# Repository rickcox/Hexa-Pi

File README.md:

# Hexa-Pi
A Compact 6 Compute Module Cluster

This is a PCB based project to create a very compact cluster of
Raspberry Pi CM4 compatible compute module boards.  It is quite bare-bones
in terms of peripheral support.  One of the modules - Module 5 - has a basic set of peripherals.
The other Modules - 0-4 - have only a small external connector for all I/O.
All 6 modules attach to a 1Gbit ethernet switch IC, which also has 2 off-board connectors.

It should be emphasized that **Compact Compute Cluster** is the focus of this design, not connectivity.
Connectivity, and peripheral support, has been reduced to meet the compact compute cluster goal.
Since all low voltage power, and the ethernet switch are on-board, a cluster of 6 Compute modules
can be supported with 1 12V DC power jack and 1 ethernet cable.
A 6 amp or larger 12V supply is recommended to support 6 running modules.

In addition, there are 2 external ethernet switch connectors, allowing boards to be "daisy chained".

The PCB is 150mm X 150mm X 1.6mm.  

A goal of this design is to be as Compute Module independent as possible, to allow
for a variety of compatible modules to be used.  Several of the Compute Module compatible
boards have been tested:

- 
  This board basically defigned the standard, so everything possible works on a Pi CM4.
  CM4 boards in the Module5 location may be either "Lite" or with EMMC.
  CM4 boards in the Module0-4 locations must have EMMC.
  
- 
  This RK3566 base board works well. 
  Rockchip processors for some odd reason must use 1.5Mbps on the serial console.  
  The pluggable EMMC modules makes setup of these boards very easy if you buy a cheap EMMC-microSD converter.

- 
  This Amlogic A311D based board is a bit faster than the Raspberry Pi CM4.
  These are a bit fussy to get setup, and OS selection is quite limited.

- 
  This RK3588 based board is **very** fast, if that is what you are looking for.
  There are "Lite" and "Full" versions of this board. Only he Full has been tested, but both should work.
  Use caution that the extra 3rd connector does not make contact with the Hexa-Pi PCB components.
  Again, Rockchip processors use 1.5Mbps on the serial console.
  OS selection is also limited here.
  Due to higher power consumption, a larger heatsink is recommended for the Radxa CM5.

- 
  **Testing TBD.**
  Not sure if serial port will work.
  The CM5 fan support is not compatible with CM4 or Hexa-Pi. The I2C fan controller can be used,
  as with a CM4

- Due to higher power consumption, a larger heatsink and possibly a heatspreader is recommended for the Raspberry Pi CM5.

Not all "compatible" boards have been tested.  
It is expected, unless the manufacturer has done something specific to make it incompatible, most "compatible" boards should work. 
Reviewing the datasheet and pinout on the 100 pin mezzanine connectors can be useful in spotting incompatibilities.

The Raspberry Pi CM4 boards have been most throughly tested.  
The other boards all have been verified to operate and connect via etherent, but all of the ports have not been tested.
Where known, incompatibilities have been noted.
It is recommended to initially configure an unfamiliar Compute Module in a Raspberry Pi CM4 IO board,
or board vendor specific baseboard, where all of the IO ports are available.
The Module5 location on the Hexa-Pi board may work for this, since it has USB, HDMI, and microSD
card support - but does not have the 40pin IO connector. 
Having a GUI is often helpful for the initial OS setup on a new board - even if your eventual use is headless.

Also, there is a small "Pi-Panel" support board that attaches to the external connectors 
at the top to provide a few simple peripherals for **all** of the Modules individually. 
A Green activity LED for each module is visible at the top, next to that module's connector.

There are also a Red power LED, a Yellow USB Overload LED, a White rpibboot mode LED, and a Blue NVME activity LED,
all on the main PCB, bottom edge.

Also included is stl files for a case for the Hexa-Pi board.
The PCB's were built, and mostly assembled, by JLCPCB.
The Case was 3D Printed. 

There is more information in the sub-directories:

- 
- 
- 

This work is licensed under the Creative Commons Attribution 4.0 International License. To view a copy of the license, visit https://creativecommons.org/licenses/by/4.0/

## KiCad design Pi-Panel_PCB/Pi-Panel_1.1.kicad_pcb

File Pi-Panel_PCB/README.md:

# Pi-Panel
A small "Front Panel" for the compute modules in the Hexa-Pi PCB.
5 of the modules have no other peripherals other than ethernet.

This is a small 36mm X 50mm PCB based that connects to the main Hexa-Pi board
using a 10 wire interface with JST connectors.

Since the individual Compute Modules on the main PCB are all powered together,
the goal with this board is to allow some basic repair and diagnosis if here are errors 
or failures on specific modules - without powering the main board down and disassembling the case!

The Activity LED for each module is adjacent and to the left of that board's conncetor.
The panel provides for each module individually:
- 5V and Gnd. Realistically about 500ma MAX can be pulled from 5V.
  **Warning** this is NOT current limited. 
  If you overload it, you will undervolt that Compute Module
- A Reset Push-Button for that specific CM.
- A serial console and CH340C USB to serial converter.
  You can directly plug into the USB-C connector and see a serial port.
  This connection uses the Raspberry 4 Compute Module serial interface pins -
  GPIO 14 (RxD) and GPIO 15(RxD). NOTE - some of the non-Raspberry Pi
  Compute modules default to different Serial console ports&pins
- A USB 2.0 port. This may be used to add any normal usb peripheral to the Pi.
  A USB Flash drive is the obvious usage, but anything USB2 compatible should work.
- An I2C port. This can be used for whatever desired.  
  This was initially envisioned as some sort of external display and maybe a couple
  buttons to control it.  Nothing has been developed here though, but
  there may be some interesting off-the-shelf options out there.
  The I2C is available on 3 Pi-Panel connectors:
  - A QWIIC Connector.
  - A Stemma-QT Style connector.
  - 0.1 inch headers.  Included is a 3.3V supply, which may be useful in some situations.
    This is a 250ma LDO off of the 5V supply, so remember the current **warning** above.

The connection to the main Hexa-Pi board uses a 10 pin JST GH 1.25mm connector.
Manufacturer partnumber SM10B-GHS-TB.  It is possible to buy pre-assembeled cables
with this mating connector. They can be purchased with connectors on both ends, or
having 1 end free.  Look for something like "GH 1.25MM 10P Single Ended" or "Double Ended".  
There are solderable holes on the Pi-Panel so the "Single Ended" type cable assemblies can be used,
and hand soldered on the Pi-Panel end.

Oh, and **one ugly secret!** The 10 pin JST connectors used between the Panel and main Hexa-Pi
board do not support any type of sequencing (Connect ground before anything else).
As a result, plugging the Pi-Panel into a running Hexa-Pi **MAY** result in the
connected Compute Module spontaneously resetting.  Being careful to have the Panel
grounded before plugging it in seems to minimize this anomaly!  
If another version of this board is done, this is on the list of things to try and fix, 
but you need to live with it for now.

This was developed in KiCad, and the design files are here.
The initial PCB's were built by JLCPCB, and partially assembled by them.
The through-hole parts and I2C connectors were hand assembled.

This PCB was small enough, that a panel of 2 was actually build.
Directory **production** has the 1 instance manufacturing data, and
directory **production-pnl** has the 2 instance manufacturing data.
At JLCPCB, both PCB's cost the same, since they are under 50mmX50mm.
The assembled 2 instance panel costs slightly more due
to the incremental cost of the parts - but you get 2 boards for the price of 1!

This work is licensed under the Creative Commons Attribution 4.0 International License. To view a copy of the license, visit https://creativecommons.org/licenses/by/4.0/

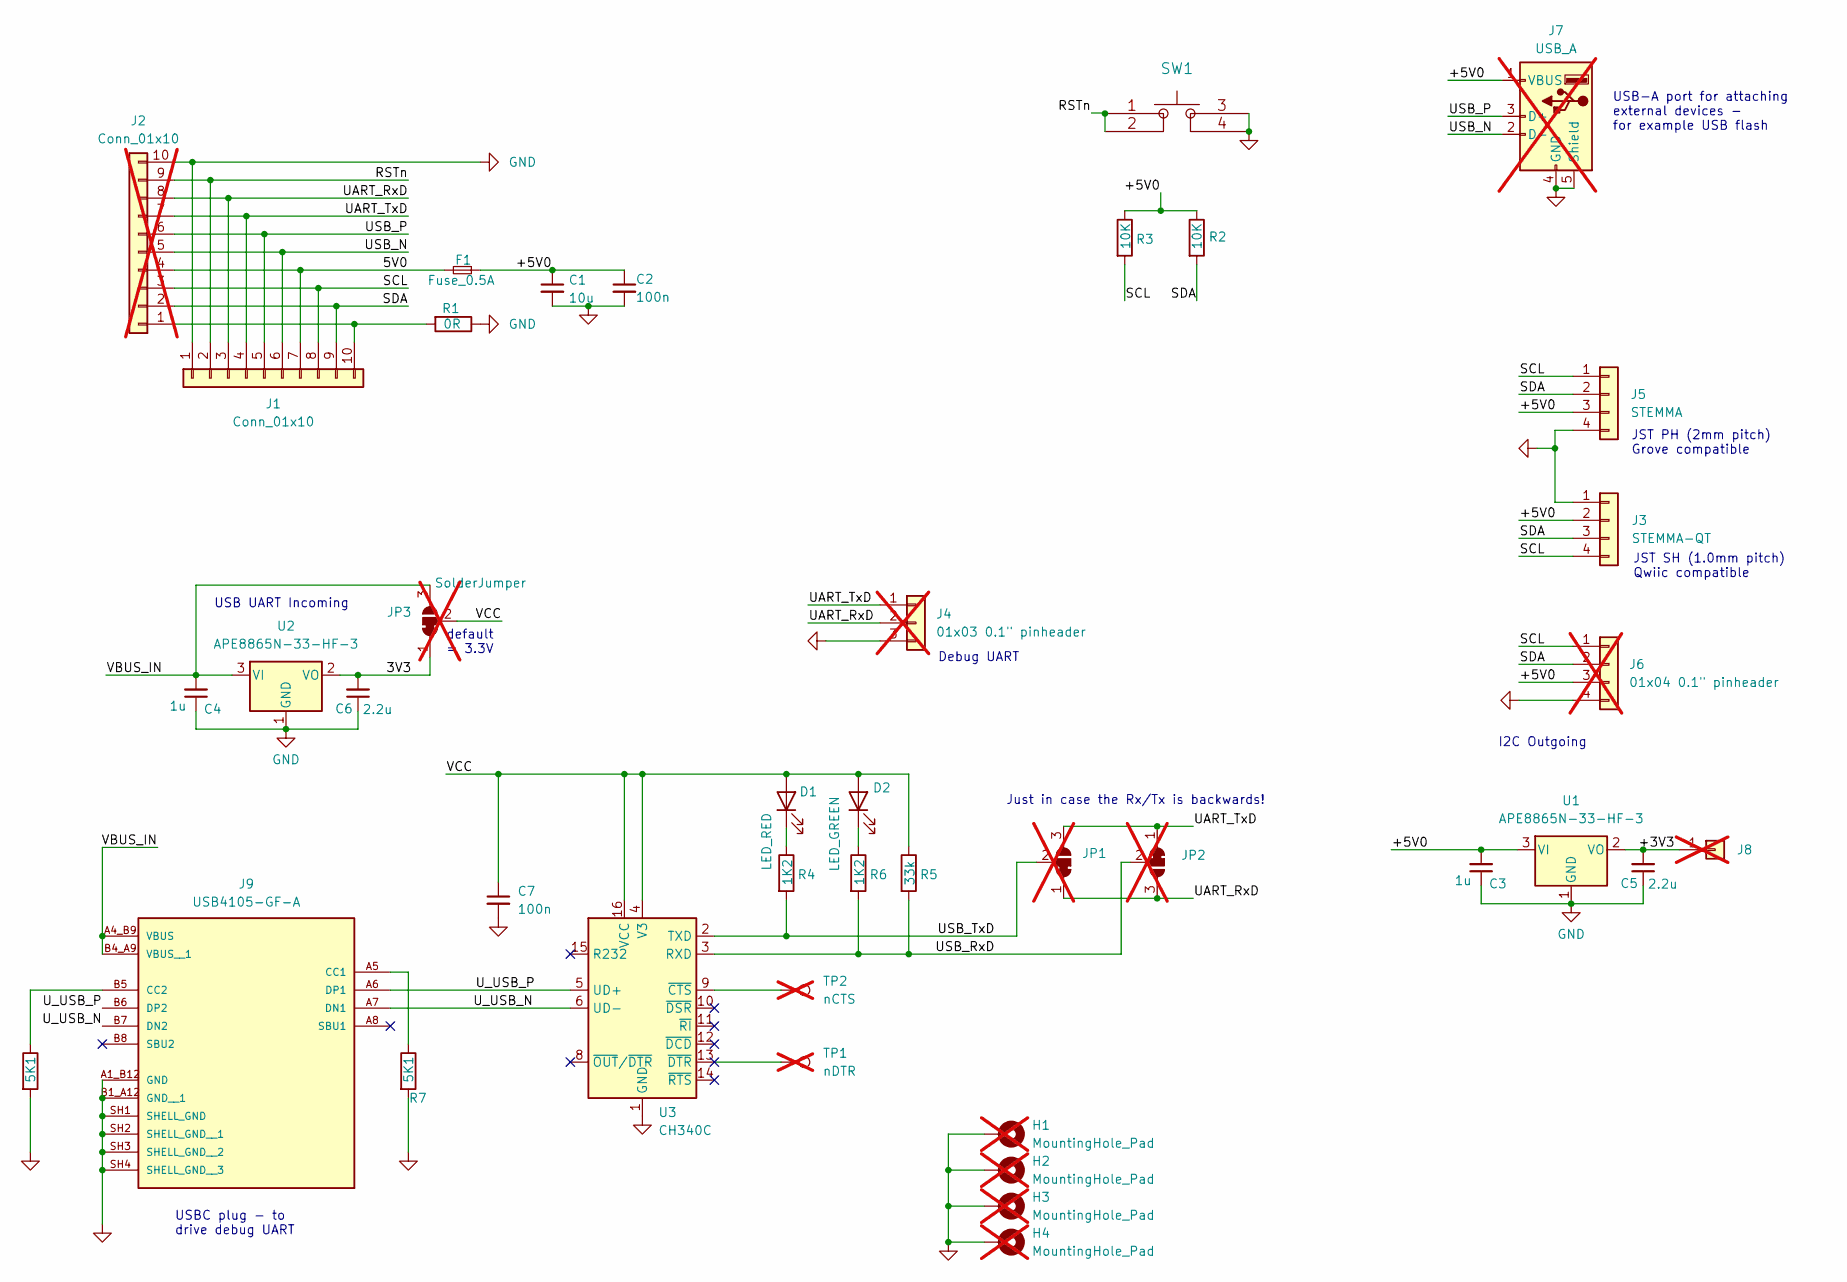
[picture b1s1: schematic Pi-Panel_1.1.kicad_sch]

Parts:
C1: 10u; C_0603_1608Metric; LCSC Part # C19702
C2, C7: 100n; C_0603_1608Metric; LCSC Part # C14663
C3, C4: 1u; C_0603_1608Metric; LCSC Part # C15849
C5, C6: 2.2u; C_0603_1608Metric; LCSC Part # C23630
D1: LED_RED; LED_0603_1608Metric; LCSC Part # C2286
D2: LED_GREEN; LED_0603_1608Metric; LCSC Part # C72038
F1: Fuse_0.5A; R_0603_1608Metric_Pad0.98x0.95mm_HandSolder; LCSC Part # C2960491
H1, H2, H3, H4: MountingHole_Pad; MountingHole_2.5mm_Pad_TopBottom; not fitted
J1: Conn_01x10; JST_GH_SM10B-GHS-TB_1x10-1MP_P1.25mm_Horizontal; Manuf Partno SM10B-GHS-TB; LCSC Part # C2683602
J2: Conn_01x10; PinHeader_1x10_P2.00mm_Vertical; not fitted
J3: STEMMA-QT; JST_SH_SM04B-SRSS-TB_1x04-1MP_P1.00mm_Horizontal; LCSC Part # C160404
J4: 01x03 0.1" pinheader; PinHeader_1x03_P2.54mm_Vertical; LCSC Part # TH; not fitted
J5: STEMMA; JST_PH_S4B-PH-SM4-TB_1x04-1MP_P2.00mm_Horizontal; LCSC Part # C265102
J6: 01x04 0.1" pinheader; PinHeader_1x04_P2.54mm_Vertical; LCSC Part # TH; not fitted
J7: USB_A; USB_A_Wuerth_614004134726_Horizontal; LCSC Part # TH; not fitted
J8: Conn_01x01; PinHeader_1x01_P2.54mm_Vertical; LCSC Part # TH; not fitted
J9: USB4105-GF-A; GCT_USB4105-GF-A; PARTREV B3; LCSC Part # C5184243
JP1, JP2, JP3: SolderJumper; SolderJumper-3_P1.3mm_Bridged12_RoundedPad1.0x1.5mm_NumberL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; not fitted
R1: 0R; R_0603_1608Metric_Pad0.98x0.95mm_HandSolder; LCSC Part # C21189
R2, R3: 10K; R_0603_1608Metric; LCSC Part # C25804
R4, R6: 1K2; R_0603_1608Metric; LCSC Part # C22765
R5: 33k; R_0603_1608Metric; LCSC Part # C4216
R7, R8: 5K1; R_0603_1608Metric; LCSC Part # C23186
SW1: pushButton-PTS647SM38SMTR2LFS; Part Description Tact Sw SPST-NO Top Actuated SMT 4.5mmX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; LCSC Part # C2689502
TP1: nDTR; TestPoint_Pad_1.0x1.0mm; not fitted
TP2: nCTS; TestPoint_Pad_1.0x1.0mm; not fitted
U1, U2: APE8865N-33-HF-3; SOT-23; LCSC Part # C296288
U3: CH340C; SOIC-16_3.9x9.9mm_P1.27mm; LCSC Part # C7464026

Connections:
/3V3: C6.2, JP3.1 (A), U2.2 (VO)
/5V0: F1.2, J1.7, J2.4
/+3V3: C5.2, J8.1, U1.2 (VO)
/+5V0: C1.1, C2.1, C3.2, F1.1, J3.2, J5.3, J6.3, J7.1 (VBUS), R2.1, R3.1, U1.3 (VI)
/RSTn: J1.2, J2.9, SW1.1, SW1.2
/SCL: J1.8, J2.3, J3.4, J5.1, J6.1, R3.2
/SDA: J1.9, J2.2, J3.3, J5.2, J6.2, R2.2
/UART_RxD: J1.3, J2.8, J4.2, JP1.1 (A), JP2.3 (B)
/UART_TxD: J1.4, J2.7, J4.1, JP1.3 (B), JP2.1 (A)
/USB_N: J1.6, J2.5, J7.2 (D-)
/USB_P: J1.5, J2.6, J7.3 (D+)
/USB_RxD: JP2.2 (C), R5.2, R6.2, U3.3 (RXD)
/USB_TxD: JP1.2 (C), R4.2, U3.2 (TXD)
/U_USB_N: J9.A7 (DN1), J9.B7 (DN2), U3.6 (UD-)
/U_USB_P: J9.A6 (DP1), J9.B6 (DP2), U3.5 (UD+)
/VBUS_IN: C4.2, J9.A4_B9 (VBUS), J9.B4_A9 (VBUS__1), JP3.3 (B), U2.3 (VI)
/VCC: C7.1, D1.2 (A), D2.2 (A), JP3.2 (C), R5.1, U3.4 (V3), U3.16 (VCC)
GND: C1.2, C2.2, C3.1, C4.1, C5.1, C6.1, C7.2, H1.1, H2.1, H3.1, H4.1, J1.1, J2.10, J3.1, J4.3, J5.4, J6.4, J7.4 (GND), J7.5 (Shield), J9.A1_B12 (GND), J9.B1_A12 (GND__1), J9.SH1 (SHELL_GND), J9.SH2 (SHELL_GND__1), J9.SH3 (SHELL_GND__2), J9.SH4 (SHELL_GND__3), R1.1, R7.2, R8.2, SW1.3, SW1.4, U1.1 (GND), U2.1 (GND), U3.1 (GND)
unnamed: D1.1 (K), R4.1
unnamed: D2.1 (K), R6.1
unnamed: J1.10, J2.1, R1.2
unnamed: J9.A5 (CC1), R7.1
unnamed: J9.B5 (CC2), R8.1
unnamed: TP2.1, U3.9 (~CTS)

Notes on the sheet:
I2C Outgoing
JST PH (2mm pitch) Grove compatible
USB-A port for attaching external devices - for example USB flash
Debug UART
USB UART Incoming
JST SH (1.0mm pitch) Qwiic compatible
default = 3.3V
USBC plug - to drive debug UART
Just in case the Rx/Tx is backwards!

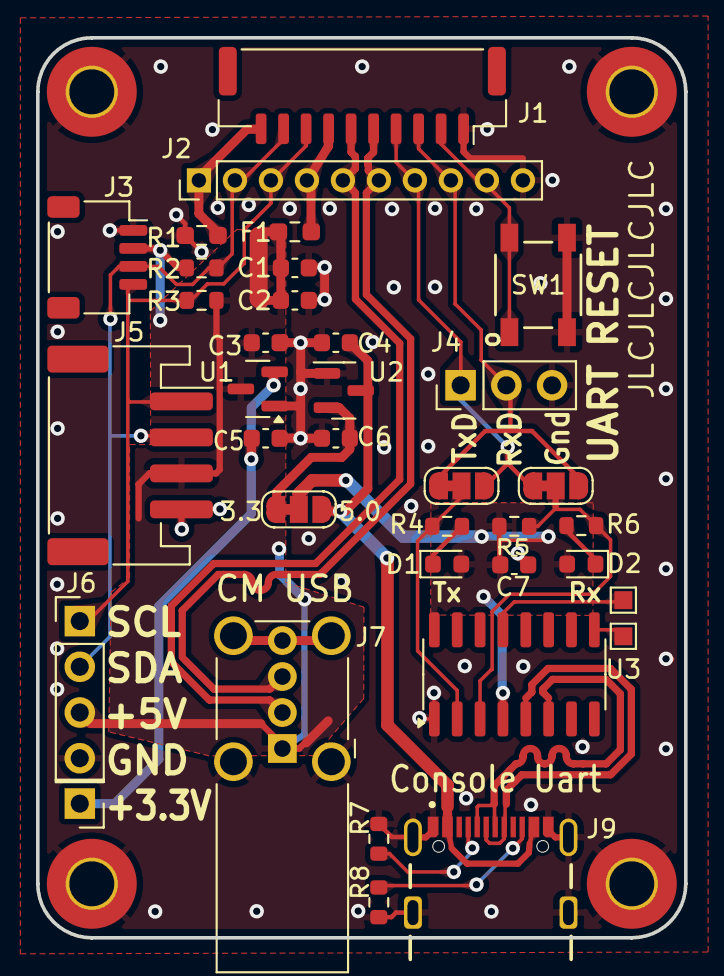
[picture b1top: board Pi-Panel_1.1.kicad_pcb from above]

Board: 2 copper layers, 36.0 x 50.0 mm, 40 parts (0 on the bottom side), 24 nets.

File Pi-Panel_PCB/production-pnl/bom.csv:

Designator,Footprint,Quantity,Value,LCSC Part #
"C1_2, C1",0603,2,10u,C19702
"C2_2, C2, C7_2, C7",0603,4,100n,C14663
"C3_2, C3, C4_2, C4",0603,4,1u,C15849
"C5_2, C5, C6_2, C6",0603,4,2.2u,C23630
"D1_2, D1",0603,2,LED_RED,C2286
"D2_2, D2",0603,2,LED_GREEN,C72038
"F1_2, F1",0603,2,Fuse_0.5A,C2960491
"J1_2, J1",JST_GH_SM10B-GHS-TB_1x10-1MP_P1.25mm_Horizontal,2,Conn_01x10,C2683602
"J3_2, J3",JST_SH_SM04B-SRSS-TB_1x04-1MP_P1.00mm_Horizontal,2,STEMMA-QT,C160404
"J5_2, J5",JST_PH_S4B-PH-SM4-TB_1x04-1MP_P2.00mm_Horizontal,2,STEMMA,C265102
"J9_2, J9",GCT_USB4105-GF-A,2,USB4105-GF-A,C5184243
"R1_2, R1",0603,2,0R,C21189
"R2_2, R2, R3_2, R3",0603,4,10K,C25804
"R4_2, R4, R6_2, R6",0603,4,1K2,C22765
"R5_2, R5",0603,2,33k,C4216
"R7_2, R7, R8_2, R8",0603,4,5K1,C23186
"SW1_2, SW1",pushButton-PTS647SM38SMTR2LFS,2,pushButton-PTS647SM38SMTR2LFS,C2689502
"U1_2, U1, U2_2, U2",SOT-23,4,APE8865N-33-HF-3,C296288
"U3_2, U3",SOIC-16_3.9x9.9mm_P1.27mm,2,CH340C,C7464026

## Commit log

2024-11-28 Update LICENSE
2024-11-28 Corrected License#
2024-11-28 Added the basics
2024-11-28 Fix Typo
2024-12-07 initialize
2024-12-07 Compress a large file
2024-12-07 Add summary picture
2024-12-07 Add README links
2024-12-07 change image file
2024-12-07 Edit README
2024-12-09 Missed File
2024-12-09 Add .gitignore
2025-01-12 Add some more possible changes
2025-03-24 Cleanup READMEs
2025-03-24 README Cleanups
2025-03-24 Improved Case Picture
2025-03-24 Better Case Picture

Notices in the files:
parts and their libraries:
Copyright 2016 Accelerated Designs. All rights reserved.
